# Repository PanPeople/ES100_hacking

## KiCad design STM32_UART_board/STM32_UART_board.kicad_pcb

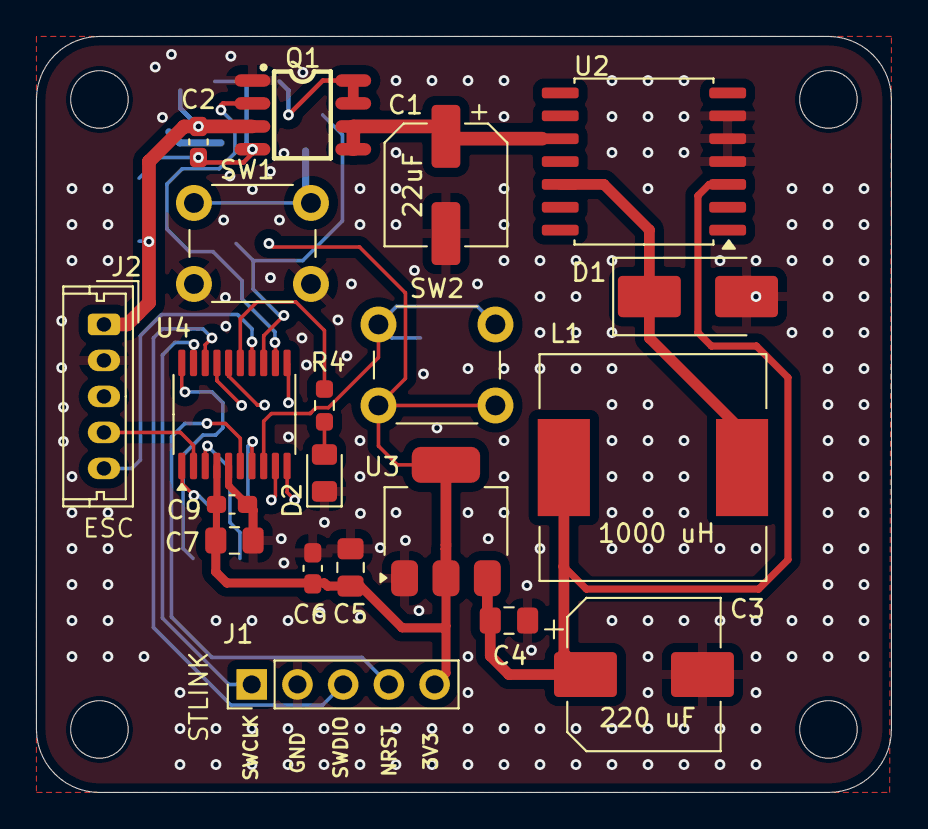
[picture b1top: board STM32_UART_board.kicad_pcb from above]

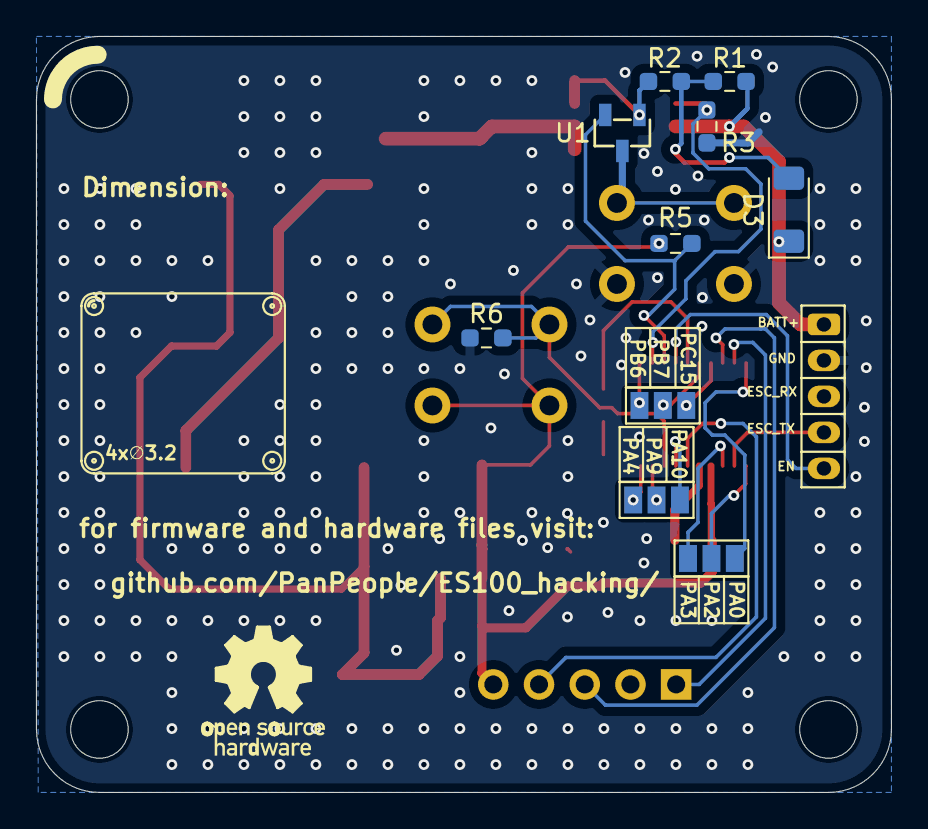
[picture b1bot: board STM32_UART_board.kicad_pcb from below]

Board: 2 copper layers, 47.5 x 42.0 mm, 34 parts (10 on the bottom side), 28 nets.

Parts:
C1: 22uF; CP_Elec_6.3x7.7
C2, C9: 100n; C_0603_1608Metric_Pad1.08x0.95mm_HandSolder
C3: 220 uF; CP_Elec_8x10
C4, C5: 22u|10V; C_0805_2012Metric_Pad1.18x1.45mm_HandSolder
C6: 100n|50V; C_0603_1608Metric_Pad1.08x0.95mm_HandSolder
C7: 4.7u; C_0805_2012Metric_Pad1.18x1.45mm_HandSolder
D1: SK26; D_SMB_Handsoldering
D2: LED; LED_0805_2012Metric_Pad1.15x1.40mm_HandSolder
D3: BZV55B15; D_MiniMELF
H1, H2, H3, H4: MountingHole; MountingHole_3.2mm_M3
J1: SWD; PinHeader_1x05_P2.54mm_Vertical
J2: Scooter; Molex_Micro-Latch_53253-0570_1x05_P2.00mm_Vertical
JP1, JP2, JP3: SolderJumper_3_Open; SolderJumper-3_P1.3mm_Open_Pad1.0x1.5mm
L1: 1000 uH; L_12x12mm_H8mm
Q1: AO4612_C4748739; SOIC-8_L4.9-W3.9-P1.27-LS6.0-BL-2
R1, R3, R4, R5, R6: 100k; R_0603_1608Metric_Pad0.98x0.95mm_HandSolder
R2: 300k; R_0603_1608Metric_Pad0.98x0.95mm_HandSolder
SW1, SW2: SW_Push; SW_PUSH_6mm
U1: BAS70-05; SOT-23-3_L2.9-W1.3-P1.90-LS2.4-BR
U2: LM2574HVM-5; SOIC-14W_7.5x9mm_P1.27mm
U3: AZ1117-3.3; SOT-223-3_TabPin2
U4: STM32C011F6Px; TSSOP-20_4.4x6.5mm_P0.65mm

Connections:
+3.3V: C5.1, C6.1, C7.1, C9.1, J1.5, R5.1, SW2.2, U3.2 (VO), U4.4 (VDD)
+5V: C3.1, C4.1, L1.2, U2.3 (FB), U3.3 (VI)
+36V: C1.1, Q1.5 (D1), Q1.6 (D1), U2.10 (VIN)
/BOOT0_USART1_RX: JP2.3 (B), U4.17 (PA10/PA12)
/BOOT0_USART1_TX: JP2.2 (C), U4.16 (PA9/PA11)
/BUTTON: R5.2, U1.2, U4.13 (PA6)
/EN: J2.5, U4.14 (PA7)
/NRST: J1.4, U4.6 (PF2)
/ON: Q1.2 (G2), R3.1, U4.12 (PA5)
/PA0: JP1.3 (B), U4.7 (PA0)
/PA1: R6.1, SW2.1, U4.8 (PA1)
/PA2: JP1.2 (C), U4.9 (PA2)
/PA3: JP1.1 (A), U4.10 (PA3)
/PA4: JP2.1 (A), U4.11 (PA4)
/PA8: R4.1, U4.15 (PA8)
/PA13: J1.3, U4.18 (PA13)
/PA14: J1.1, U4.19 (PA14)
/PB6: JP3.1 (A), U4.20 (PB6)
/PB7: JP3.2 (C), U4.1 (PB7)
/PC14: J2.4, U4.2 (PC14)
/PC15: JP3.3 (B), U4.3 (PC15)
/Q1_D2: Q1.7 (D2), Q1.8 (D2), R2.2, U1.1
/Q1_G1: C2.2, D3.2 (A), Q1.4 (G1), R1.2, R2.1
BATT+: C2.1, D3.1 (K), J2.1, Q1.3 (S1), R1.1
GND: C1.2, C3.2, C4.2, C5.2, C6.2, C7.2, C9.2, D1.2 (A), D2.1 (K), J1.2, J2.2, Q1.1 (S2), R3.2, R6.2, SW1.2, U2.4 (SGND), U2.5 (~ON/OFF), U2.6 (PGND), U3.1 (GND), U4.5 (VSS)
unnamed: D1.1 (K), L1.1, U2.12 (OUT)
unnamed: D2.2 (A), R4.2
unnamed: SW1.1, U1.3

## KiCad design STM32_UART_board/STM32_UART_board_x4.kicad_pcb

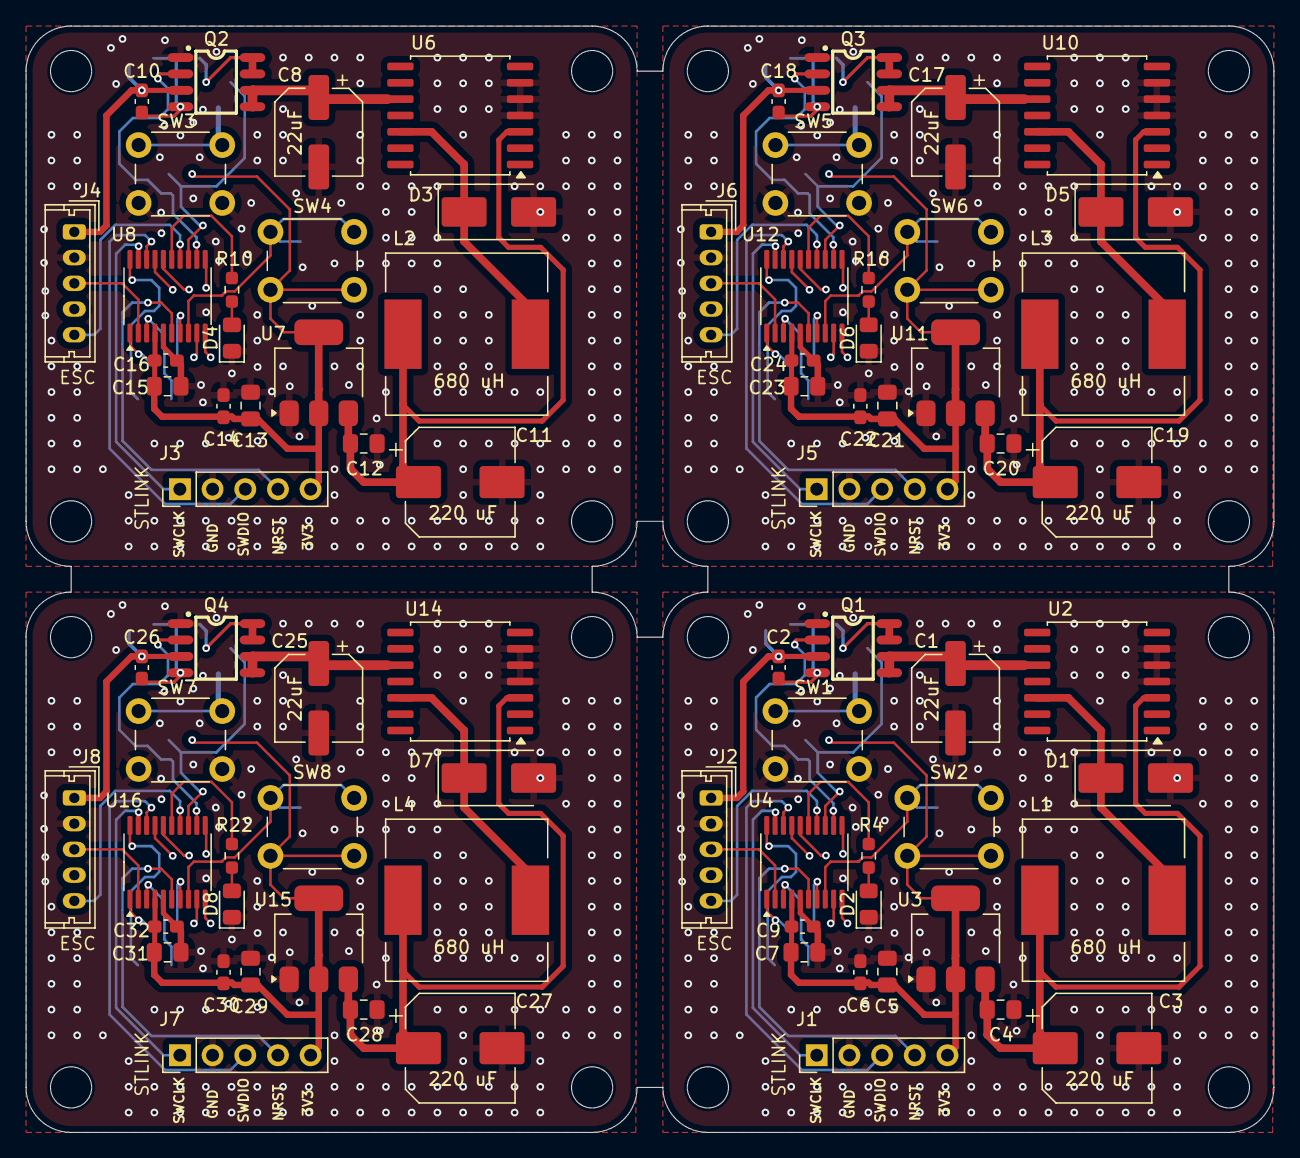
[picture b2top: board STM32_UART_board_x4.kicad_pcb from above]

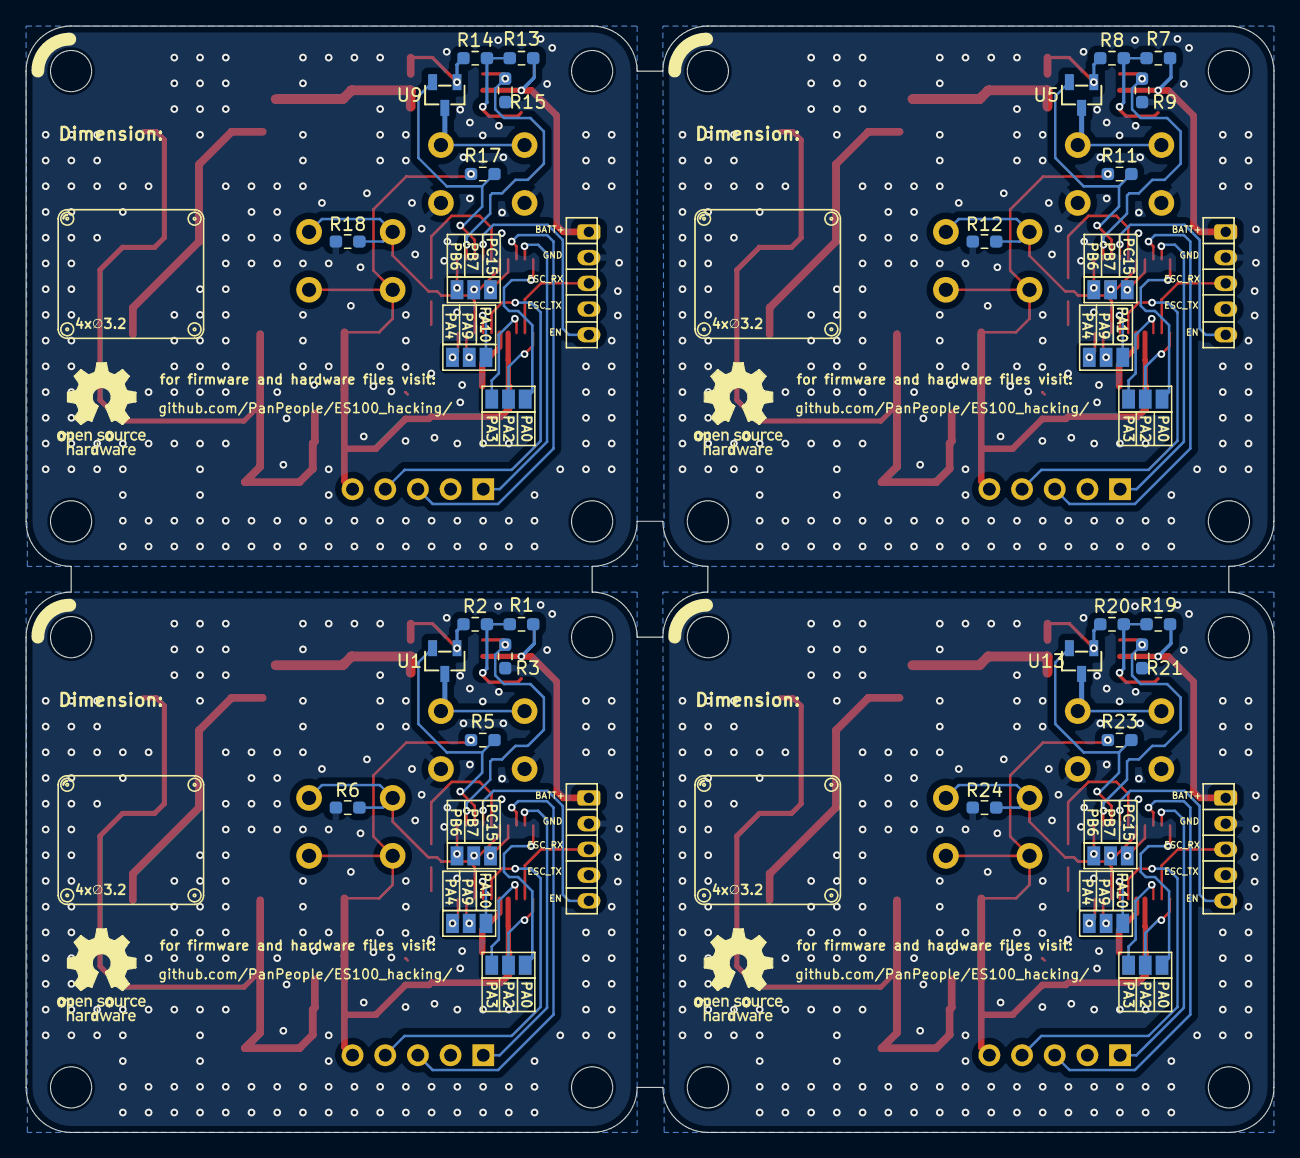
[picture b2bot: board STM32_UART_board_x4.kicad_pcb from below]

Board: 2 copper layers, 97.0 x 86.0 mm, 132 parts (36 on the bottom side), 29 nets.

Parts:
C1, C8, C17, C25: 22uF; CP_Elec_6.3x7.7
C2, C9, C10, C16, C18, C24, C26, C32: 100n; C_0603_1608Metric_Pad1.08x0.95mm_HandSolder
C3, C11, C19, C27: 220 uF; CP_Elec_8x10
C4, C5, C12, C13, C20, C21, C28, C29: 22u|10V; C_0805_2012Metric_Pad1.18x1.45mm_HandSolder
C6, C14, C22, C30: 100n|50V; C_0603_1608Metric_Pad1.08x0.95mm_HandSolder
C7, C15, C23, C31: 4.7u; C_0805_2012Metric_Pad1.18x1.45mm_HandSolder
D1, D3, D5, D7: SK26; D_SMB_Handsoldering
D2, D4, D6, D8: LED; LED_0805_2012Metric_Pad1.15x1.40mm_HandSolder
H1, H2, H3, H4, H5, H6, H7, H8, H9, H10, H11, H12, H13, H14, H15, H16: MountingHole; MountingHole_3.2mm_M3
J1, J3, J5, J7: SWD; PinHeader_1x05_P2.54mm_Vertical
J2, J4, J6, J8: Scooter; Molex_Micro-Latch_53253-0570_1x05_P2.00mm_Vertical
JP1, JP2, JP3, JP4, JP5, JP6, JP7, JP8, JP9, JP10, JP11, JP12: SolderJumper_3_Open; SolderJumper-3_P1.3mm_Open_Pad1.0x1.5mm
L1, L2, L3, L4: 680 uH; L_12x12mm_H8mm
Q1, Q2, Q3, Q4: AO4612_C4748739; SOIC-8_L4.9-W3.9-P1.27-LS6.0-BL-2
R1, R3, R4, R5, R6, R7, R9, R10, R11, R12, R13, R15, R16, R17, R18, R19, R21, R22, R23, R24: 100k; R_0603_1608Metric_Pad0.98x0.95mm_HandSolder
R2, R8, R14, R20: 300k; R_0603_1608Metric_Pad0.98x0.95mm_HandSolder
SW1, SW2, SW3, SW4, SW5, SW6, SW7, SW8: SW_Push; SW_PUSH_6mm
U1, U5, U9, U13: BAS70-05; SOT-23-3_L2.9-W1.3-P1.90-LS2.4-BR
U2, U6, U10, U14: LM2574HVM-5; SOIC-14W_7.5x9mm_P1.27mm
U3, U7, U11, U15: AZ1117-3.3; SOT-223-3_TabPin2
U4, U8, U12, U16: STM32C011F6Px; TSSOP-20_4.4x6.5mm_P0.65mm

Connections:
+3.3V: C5.1, C6.1, C7.1, C9.1, C13.1, C14.1, C15.1, C16.1, C21.1, C22.1, C23.1, C24.1, C29.1, C30.1, C31.1, C32.1, J1.5, J3.5, J5.5, J7.5, R5.1, R11.1, R17.1, R23.1, SW2.2, SW4.2, SW6.2, SW8.2, U3.2 (VO), U4.4 (VDD), U7.2 (VO), U8.4 (VDD), U11.2 (VO), U12.4 (VDD), U15.2 (VO), U16.4 (VDD)
+5V: C3.1, C4.1, C11.1, C12.1, C19.1, C20.1, C27.1, C28.1, L1.2, L2.2, L3.2, L4.2, U2.3 (FB), U3.3 (VI), U6.3 (FB), U7.3 (VI), U10.3 (FB), U11.3 (VI), U14.3 (FB), U15.3 (VI)
+36V: C1.1, C8.1, C17.1, C25.1, Q1.5 (D1), Q1.6 (D1), Q2.5 (D1), Q2.6 (D1), Q3.5 (D1), Q3.6 (D1), Q4.5 (D1), Q4.6 (D1), U2.10 (VIN), U6.10 (VIN), U10.10 (VIN), U14.10 (VIN)
/BOOT0_USART1_RX: JP2.3 (B), JP5.3 (B), JP8.3 (B), JP11.3 (B), U4.17 (PA10/PA12), U8.17 (PA10/PA12), U12.17 (PA10/PA12), U16.17 (PA10/PA12)
/BOOT0_USART1_TX: JP2.2 (C), JP5.2 (C), JP8.2 (C), JP11.2 (C), U4.16 (PA9/PA11), U8.16 (PA9/PA11), U12.16 (PA9/PA11), U16.16 (PA9/PA11)
/BUTTON: R5.2, R11.2, R17.2, R23.2, U1.2, U4.13 (PA6), U5.2, U8.13 (PA6), U9.2, U12.13 (PA6), U13.2, U16.13 (PA6)
/EN: J2.5, J4.5, J6.5, J8.5, U4.14 (PA7), U8.14 (PA7), U12.14 (PA7), U16.14 (PA7)
/NRST: J1.4, J3.4, J5.4, J7.4, U4.6 (PF2), U8.6 (PF2), U12.6 (PF2), U16.6 (PF2)
/ON: Q1.2 (G2), Q2.2 (G2), Q3.2 (G2), Q4.2 (G2), R3.1, R9.1, R15.1, R21.1, U4.12 (PA5), U8.12 (PA5), U12.12 (PA5), U16.12 (PA5)
/PA0: JP1.3 (B), JP4.3 (B), JP7.3 (B), JP10.3 (B), U4.7 (PA0), U8.7 (PA0), U12.7 (PA0), U16.7 (PA0)
/PA1: R6.1, R12.1, R18.1, R24.1, SW2.1, SW4.1, SW6.1, SW8.1, U4.8 (PA1), U8.8 (PA1), U12.8 (PA1), U16.8 (PA1)
/PA2: JP1.2 (C), JP4.2 (C), JP7.2 (C), JP10.2 (C), U4.9 (PA2), U8.9 (PA2), U12.9 (PA2), U16.9 (PA2)
/PA3: JP1.1 (A), JP4.1 (A), JP7.1 (A), JP10.1 (A), U4.10 (PA3), U8.10 (PA3), U12.10 (PA3), U16.10 (PA3)
/PA4: JP2.1 (A), JP5.1 (A), JP8.1 (A), JP11.1 (A), U4.11 (PA4), U8.11 (PA4), U12.11 (PA4), U16.11 (PA4)
/PA8: R4.1, R10.1, R16.1, R22.1, U4.15 (PA8), U8.15 (PA8), U12.15 (PA8), U16.15 (PA8)
/PA13: J1.3, J3.3, J5.3, J7.3, U4.18 (PA13), U8.18 (PA13), U12.18 (PA13), U16.18 (PA13)
/PA14: J1.1, J3.1, J5.1, J7.1, U4.19 (PA14), U8.19 (PA14), U12.19 (PA14), U16.19 (PA14)
/PB6: JP3.1 (A), JP6.1 (A), JP9.1 (A), JP12.1 (A), U4.20 (PB6), U8.20 (PB6), U12.20 (PB6), U16.20 (PB6)
/PB7: JP3.2 (C), JP6.2 (C), JP9.2 (C), JP12.2 (C), U4.1 (PB7), U8.1 (PB7), U12.1 (PB7), U16.1 (PB7)
/PC14: J2.3, J4.3, J6.3, J8.3, U4.2 (PC14), U8.2 (PC14), U12.2 (PC14), U16.2 (PC14)
/PC15: JP3.3 (B), JP6.3 (B), JP9.3 (B), JP12.3 (B), U4.3 (PC15), U8.3 (PC15), U12.3 (PC15), U16.3 (PC15)
/Q1_D2: Q1.7 (D2), Q1.8 (D2), Q2.7 (D2), Q2.8 (D2), Q3.7 (D2), Q3.8 (D2), Q4.7 (D2), Q4.8 (D2), R2.2, R8.2, R14.2, R20.2, U1.1, U5.1, U9.1, U13.1
/Q1_G1: C2.2, C10.2, C18.2, C26.2, Q1.4 (G1), Q2.4 (G1), Q3.4 (G1), Q4.4 (G1), R1.2, R2.1, R7.2, R8.1, R13.2, R14.1, R19.2, R20.1
/SCOOTER_TX: J2.4, J4.4, J6.4, J8.4
BATT+: C2.1, C10.1, C18.1, C26.1, J2.1, J4.1, J6.1, J8.1, Q1.3 (S1), Q2.3 (S1), Q3.3 (S1), Q4.3 (S1), R1.1, R7.1, R13.1, R19.1
GND: C1.2, C3.2, C4.2, C5.2, C6.2, C7.2, C8.2, C9.2, C11.2, C12.2, C13.2, C14.2, C15.2, C16.2, C17.2, C19.2, C20.2, C21.2, C22.2, C23.2, C24.2, C25.2, C27.2, C28.2, C29.2, C30.2, C31.2, C32.2, D1.2 (A), D2.1 (K), D3.2 (A), D4.1 (K), D5.2 (A), D6.1 (K), D7.2 (A), D8.1 (K), J1.2, J2.2, J3.2, J4.2, J5.2, J6.2, J7.2, J8.2, Q1.1 (S2), Q2.1 (S2), Q3.1 (S2), Q4.1 (S2), R3.2, R6.2, R9.2, R12.2, R15.2, R18.2, R21.2, R24.2, SW1.2, SW3.2, SW5.2, SW7.2, U2.4 (SGND), U2.5 (~ON/OFF), U2.6 (PGND), U3.1 (GND), U4.5 (VSS), U6.4 (SGND), U6.5 (~ON/OFF), U6.6 (PGND), U7.1 (GND), U8.5 (VSS), U10.4 (SGND), U10.5 (~ON/OFF), U10.6 (PGND), U11.1 (GND), U12.5 (VSS), U14.4 (SGND), U14.5 (~ON/OFF), U14.6 (PGND), U15.1 (GND), U16.5 (VSS)
unnamed: D1.1 (K), D3.1 (K), D5.1 (K), D7.1 (K), L1.1, L2.1, L3.1, L4.1, U2.12 (OUT), U6.12 (OUT), U10.12 (OUT), U14.12 (OUT)
unnamed: D2.2 (A), D4.2 (A), D6.2 (A), D8.2 (A), R4.2, R10.2, R16.2, R22.2
unnamed: SW1.1, SW3.1, SW5.1, SW7.1, U1.3, U5.3, U9.3, U13.3

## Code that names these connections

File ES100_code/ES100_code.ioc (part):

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Mcu.Name=STM32C011F(4-6)Px
Mcu.Package=TSSOP20
Mcu.UserName=STM32C011F6Px
PA13.Mode=Serial_Wire
PA13.Signal=DEBUG_SWDIO
PA14-BOOT0.Mode=Serial_Wire
PA14-BOOT0.Signal=DEBUG_SWCLK
PA5.GPIOParameters=GPIO_Label
PA5.GPIO_Label=ON
PA5.Signal=GPIO_Output
PA6.GPIOParameters=GPIO_Label
PA6.GPIO_Label=BUTTON
PA6.Signal=GPIO_Input
PA7.GPIOParameters=GPIO_Label
PA7.GPIO_Label=EN
PA7.Signal=GPIO_Output
PA8.GPIOParameters=GPIO_Label
PA8.GPIO_Label=LED
PA8.Signal=GPIO_Output
PB7.Mode=Asynchronous
PB7.Signal=USART1_RX
PC14-OSCX_IN\ (PC14).Mode=Asynchronous
PC14-OSCX_IN\ (PC14).Signal=USART1_TX
RCC.HSE_VALUE=8000000
RCC.SYSCLKFreq_VALUE=24000000
board=custom

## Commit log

2024-11-11 added scheme of UART board
2025-07-30 schematic mostly done
2025-08-01 added footprints
2025-08-01 component placemnt 15%
2025-08-01 component placement 16%
2025-08-05 dc dc layout done
2025-08-05 almost done
2025-08-08 added testpoints to the remaining pins
2025-08-10 done xD
2025-10-03 PCB with swapped RX TX | initial code fot STM32C011
2025-10-03 minor PCB changes
